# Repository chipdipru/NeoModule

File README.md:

# NeoModule
video1

video2

video3

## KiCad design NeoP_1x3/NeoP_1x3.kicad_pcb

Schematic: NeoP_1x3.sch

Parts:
C1: 4,7uF; CP_EIA-3216-18_Kemet-A_Pad1.58x1.35mm_HandSolder
D1, D2, D3: LED_PAD; LED_1W_3W_R8
J1: Conn_01x06_Male; Pin_Header_Straight_1x06
J2, J3: Conn_01x03_Female; Socket_Strip_Straight_1x03
Q1, Q2, Q3: IRLML2060TRPBF; SOT-23
Q4, Q5, Q6: MMBT2222A; SOT-23
R1, R2, R3: 47k; R_0603_1608Metric_Pad1.05x0.95mm_HandSolder
R4, R5, R6: 1,8R; R_1206_HandSoldering
R7: 4,7k; R_0603_1608Metric_Pad1.05x0.95mm_HandSolder
TH1: Thermistor_NTC; R_0603_1608Metric_Pad1.05x0.95mm_HandSolder

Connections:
+5V: D1.2, D1.3, D2.2, D2.3, D3.2, D3.3, J1.6, J2.2, J3.2, R7.2
B: J1.2, R3.2
G: J1.3, R2.2
GND: C1.2, J1.5, J2.3, J3.3, Q4.2 (C), Q5.2 (C), Q6.2 (C), R4.1, R5.1, R6.1, TH1.2
unnamed: D1.1, Q1.3 (D)
unnamed: D2.1, Q2.3 (D)
unnamed: D3.1, Q3.3 (D)
unnamed: Q1.1 (G), Q4.3 (E), R1.1
unnamed: Q1.2 (S), Q4.1 (B), R4.2
unnamed: Q2.1 (G), Q5.3 (E), R2.1
unnamed: Q2.2 (S), Q5.1 (B), R5.2
unnamed: Q3.1 (G), Q6.3 (E), R3.1
unnamed: Q3.2 (S), Q6.1 (B), R6.2
R: J1.4, R1.2
TC: C1.1, J1.1, R7.1, TH1.1

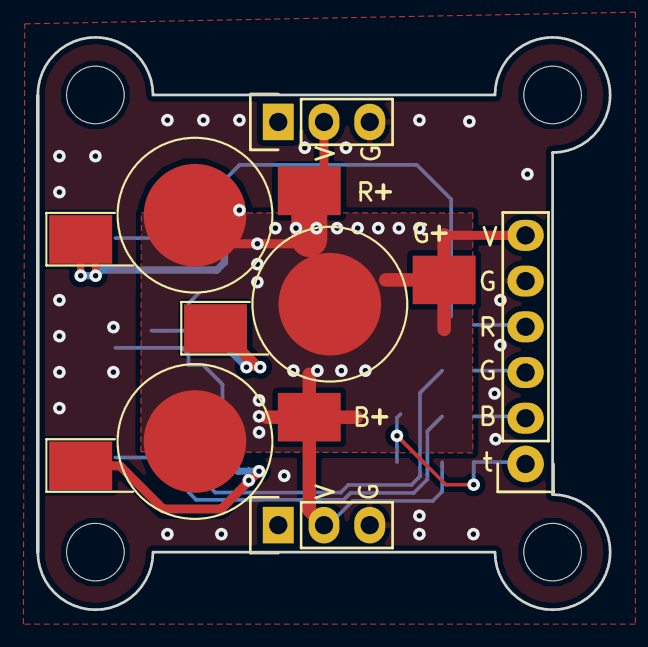
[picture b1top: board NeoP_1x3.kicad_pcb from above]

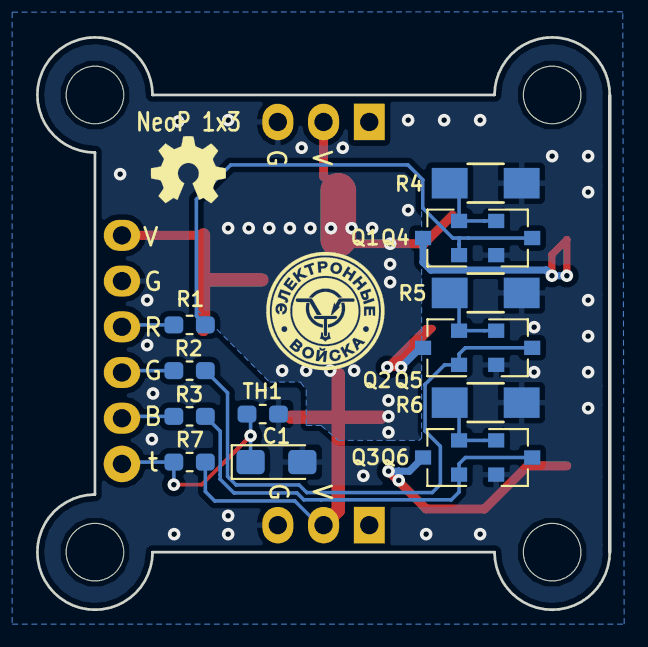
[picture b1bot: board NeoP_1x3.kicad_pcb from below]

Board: 2 copper layers, 31.8 x 31.8 mm, 21 parts (15 on the bottom side), 15 nets.

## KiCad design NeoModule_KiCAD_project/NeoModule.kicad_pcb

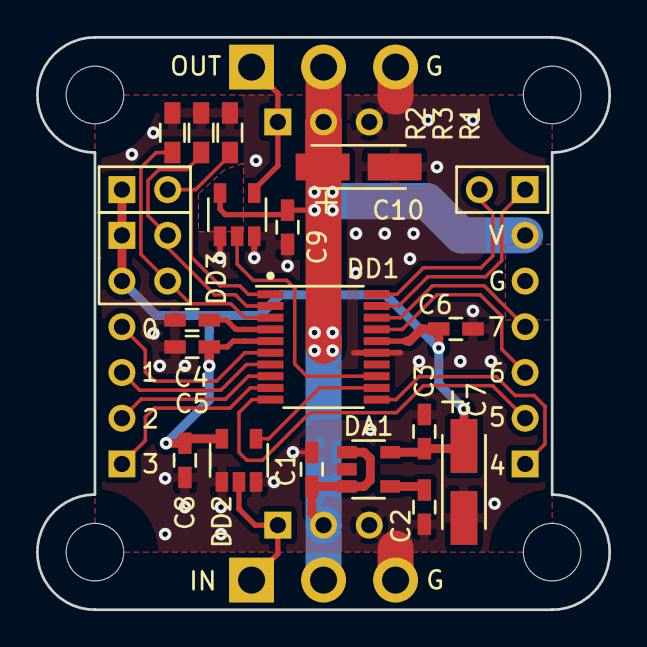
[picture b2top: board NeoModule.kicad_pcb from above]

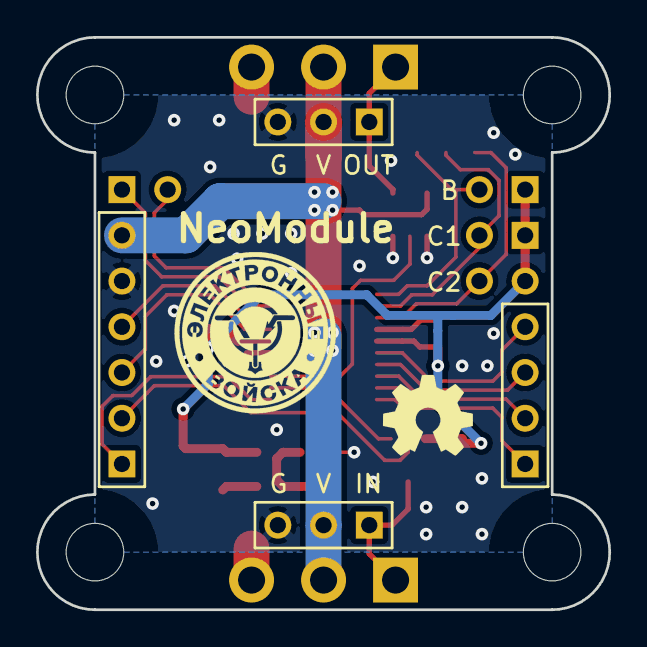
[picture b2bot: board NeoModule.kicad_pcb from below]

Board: 2 copper layers, 31.8 x 31.8 mm, 24 parts (4 on the bottom side), 22 nets.

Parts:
C1, C3: 2,2мкФ; C_0603_HandSoldering
C2: 0,01мкФ; C_0603_HandSoldering
C4, C5, C6, C8, C9: 0,1мкФ; C_0603_HandSoldering
C7, C10: 10мкФ; TantalC_SizeA_EIA-3216_HandSoldering_mm
DA1: LP2985-3.3; SOT-23-5_mm
DD1: STM32F030F4Px; TSSOP-20_4.4x6.5mm_Pitch0.65mm
DD2: MC74VHC1GT125; SOT-23-5_mm
DD3: 74AHC1G125; SOT-23-5_mm
R1, R2, R3: 10k; R_0603_HandSoldering
XP1: Conn_02x02_Odd_Even; Pin_Header_Straight_2x02_mm
XP2, XP5: Conn_01x02; Pin_Header_Straight_1x02_mm
XP3: Conn_01x04; Pin_Header_Straight_1x04_mm
XP4: Conn_01x06; Pin_Header_Straight_1x06_mm
XP6, XP7: Conn_01x03; Pin_Header_Straight_1x03_mm

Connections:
3V3: C3.1, C5.2, C6.2, C7.1, C8.2, DA1.5, DD1.5, DD1.16, DD2.5, XP1.1, XP1.3, XP2.1
DIN: DD2.2, XP6.1
DOUT: DD3.4, XP7.1
GND: C1.2, C2.2, C3.2, C4.2, C5.1, C6.1, C7.2, C8.1, C9.1, C10.2, DA1.2, DD1.15, DD2.1, DD2.3, DD3.1, DD3.3, R1.2, R2.1, R3.1, XP4.5, XP6.3, XP7.3
LED_IN: DD1.12, DD2.4
LED_OUT: DD1.13, DD3.2
unnamed: C2.1, DA1.4
unnamed: C4.1, DD1.4
unnamed: DD1.1, R1.1, XP2.2
unnamed: DD1.2, R3.2, XP1.2
unnamed: DD1.3, R2.2, XP1.4
OUT1: DD1.6, XP3.4
OUT2: DD1.7, XP3.3
OUT3: DD1.8, XP3.2
OUT4: DD1.9, XP3.1
OUT5: DD1.11, XP4.1
OUT6: DD1.10, XP4.2
OUT7_TX: DD1.17, XP4.3
OUT8_RX: DD1.18, XP4.4
SWDCLK: DD1.20, XP5.2
SWDIO: DD1.19, XP5.1
VIN: C1.1, C9.2, C10.1, DA1.1, DA1.3, DD3.5, XP4.6, XP6.2, XP7.2

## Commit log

2018-11-20 KiCad project PCB
2018-11-20 IAR project
2018-11-20 firmware for STM32F030F4P6
2018-11-21 Board for three LEDs. 3x1W. KiCad project
2018-11-21 Board for RGB LED. 1x3W. KiCad project
2018-12-29 VU meter
2018-12-29 VU meter back light
2018-12-29 VU meter IAR project
2018-12-29 VU meter black
